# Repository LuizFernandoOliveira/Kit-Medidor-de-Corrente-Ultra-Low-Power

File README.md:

# Kit Medidor de Corrente Ultra-Low Power

## Descrição
Contendo quatro circuitos independentes de quatro topologias distintas, este circuito eletrônico é ideal para realizar a medição de corrente elétrica de diversas aplicação ultra-low power.

---

## Descrições técnicas

- Possui quatro circuitos independentes de corrente via transimpedância;
- Possui quatro circuitos independentes de corrente via rede T;
- Possui quatro circuitos independentes de corrente via High-Side;
- Possui quatro circuitos independentes de corrente via Low-Side;
- Possui alimentação de 3V3 ou 5V;
- Possui alimentação via USB tipo-C;
- Altíssima precisão e estabilidade: tensão de offset de 5 µV máx. a 25 °C, 8 µV em toda a faixa de temperatura (-40 °C a 125 °C);
- Entrada e saída rail-to-rail;
- Baixa tensão de alimentação: 1,8 - 5,5 V;
- Baixo consumo de energia: 40 µA máx. a 5 V;
- Produto ganho-largura de banda: 400 kHz;
- Alta tolerância a ESD: 4 kV HBM;
- Ampla faixa de temperatura de operação: -40 a 125 °C

---

## Estrutura do repositório
Os arquivos de hardware foram desenvolvidos utilizando o KiCad 9.0.
- **`.kicad_pcb`**: Layout da placa de circuito impresso (Board).
- **`.kicad_sch`**: Esquemático eletrônico do sistema (Schematic).
- **`.kicad_pro`**: Gerenciador de projeto do KiCad (Project).

---

## Autor
**Dr. Luiz Fernando Pinto de Oliveira**

*Engenheiro Eletrônico especializado em Sistemas Embarcados e Ultra-Low Power.*
- **Website:** [FAPLO](https://faplo.webnode.page/)
- **LinkedIn:** [lfpo](https://www.linkedin.com/in/lfpo/)

---

Shield: [![CC BY-NC-ND 4.0][cc-by-nc-nd-shield]][cc-by-nc-nd]

This work is licensed under a
[Creative Commons Attribution-NonCommercial-NoDerivs 4.0 International License][cc-by-nc-nd].

[![CC BY-NC-ND 4.0][cc-by-nc-nd-image]][cc-by-nc-nd]

[cc-by-nc-nd]: http://creativecommons.org/licenses/by-nc-nd/4.0/
[cc-by-nc-nd-image]: https://licensebuttons.net/l/by-nc-nd/4.0/88x31.png
[cc-by-nc-nd-shield]: https://img.shields.io/badge/License-CC%20BY--NC--ND%204.0-lightgrey.svg

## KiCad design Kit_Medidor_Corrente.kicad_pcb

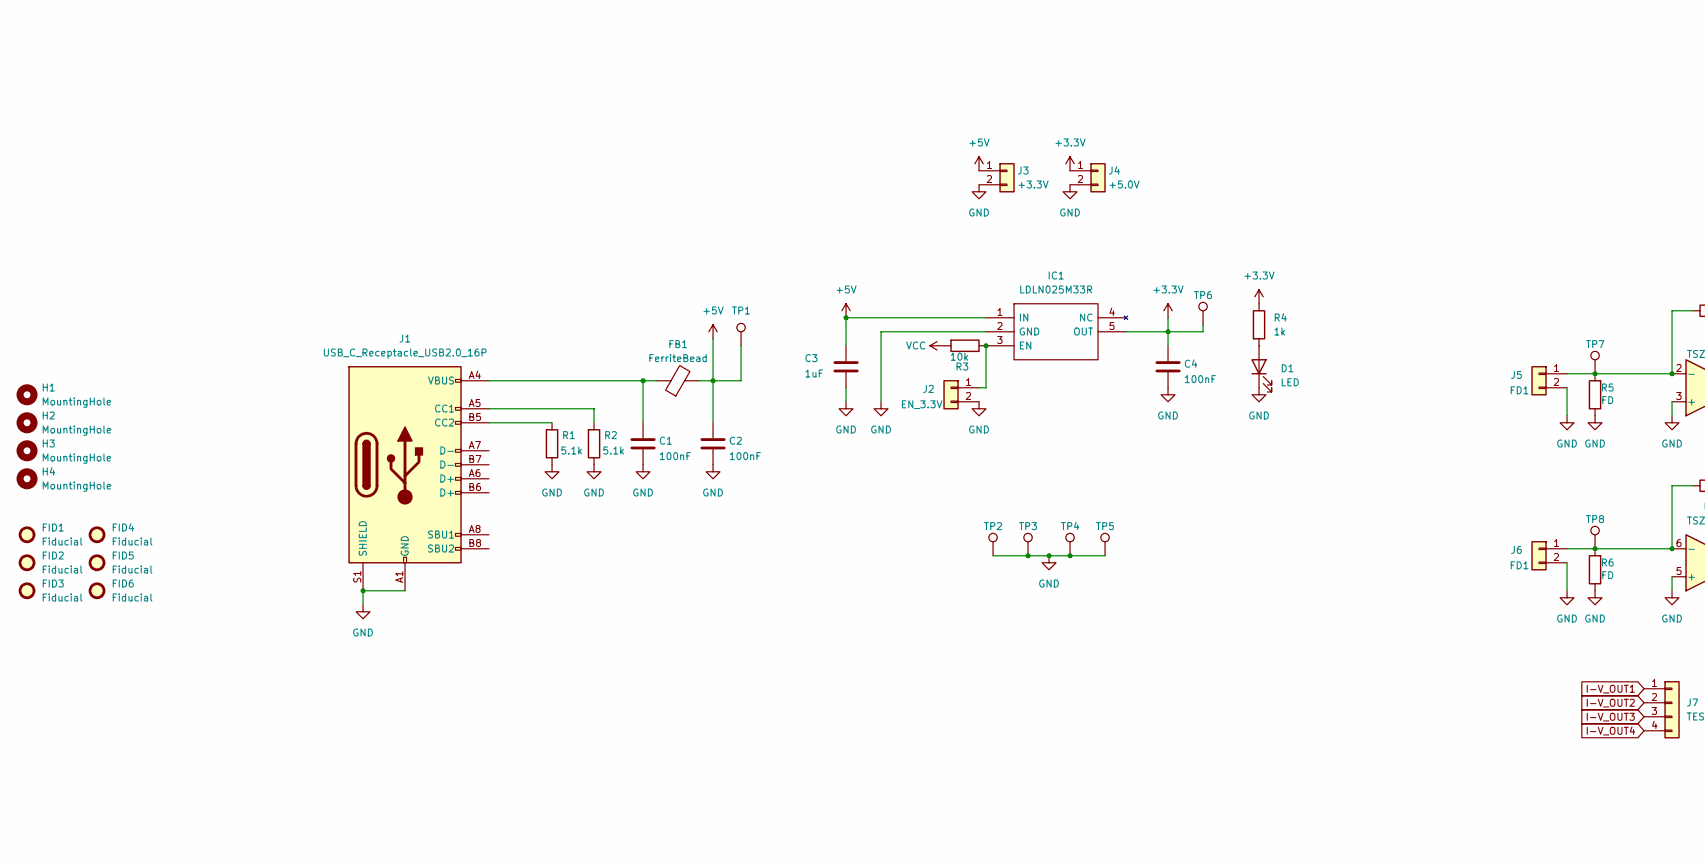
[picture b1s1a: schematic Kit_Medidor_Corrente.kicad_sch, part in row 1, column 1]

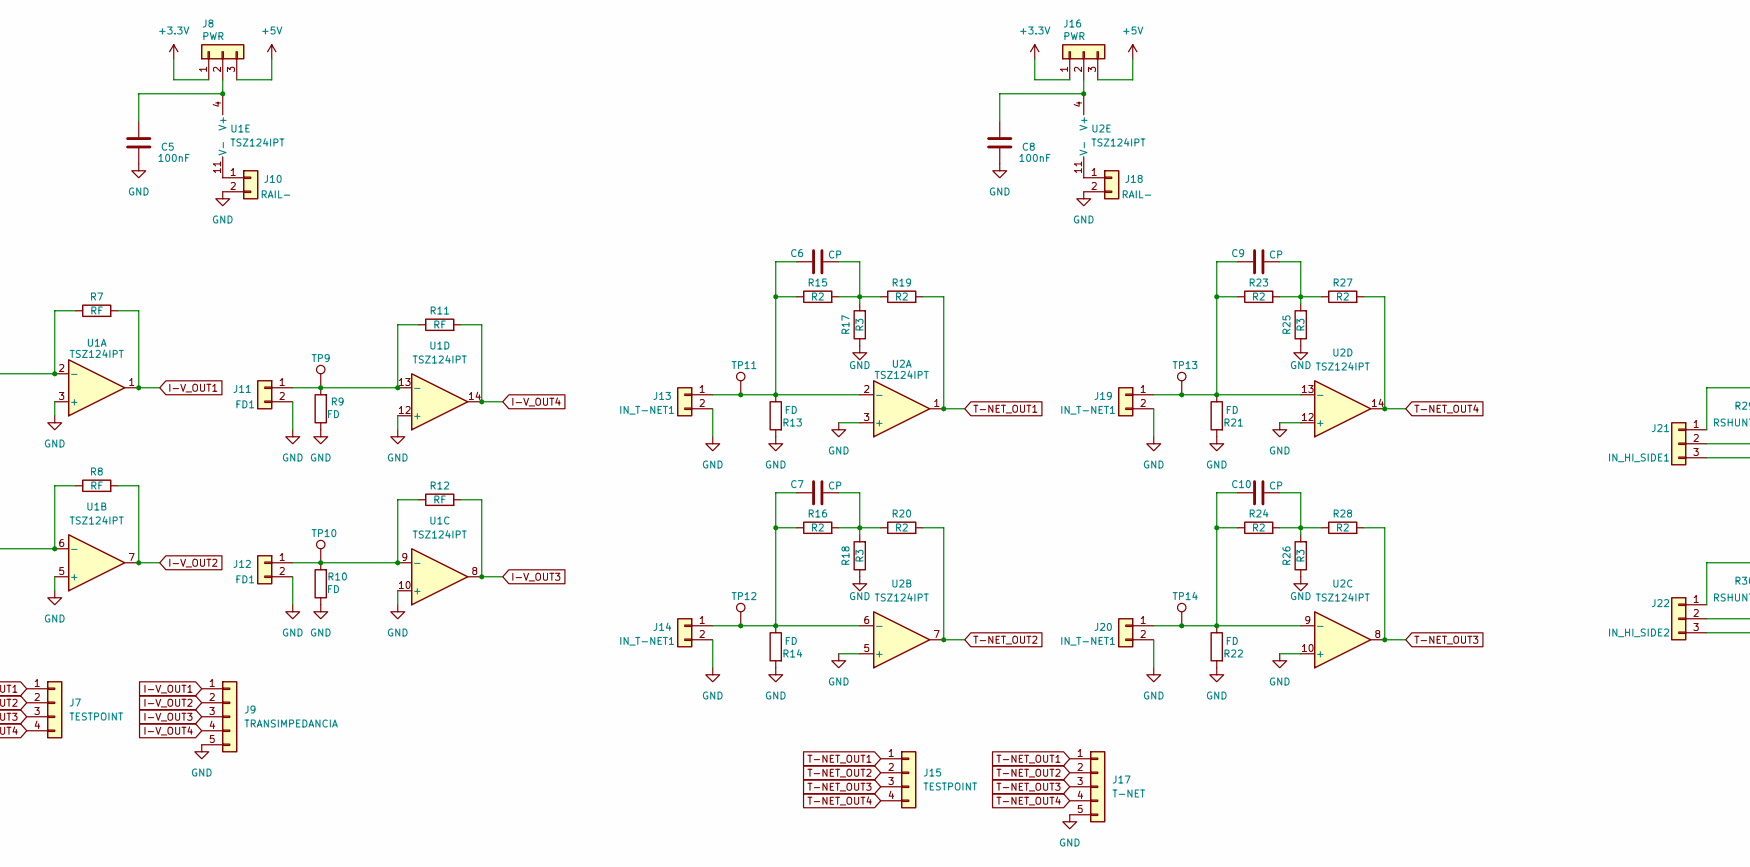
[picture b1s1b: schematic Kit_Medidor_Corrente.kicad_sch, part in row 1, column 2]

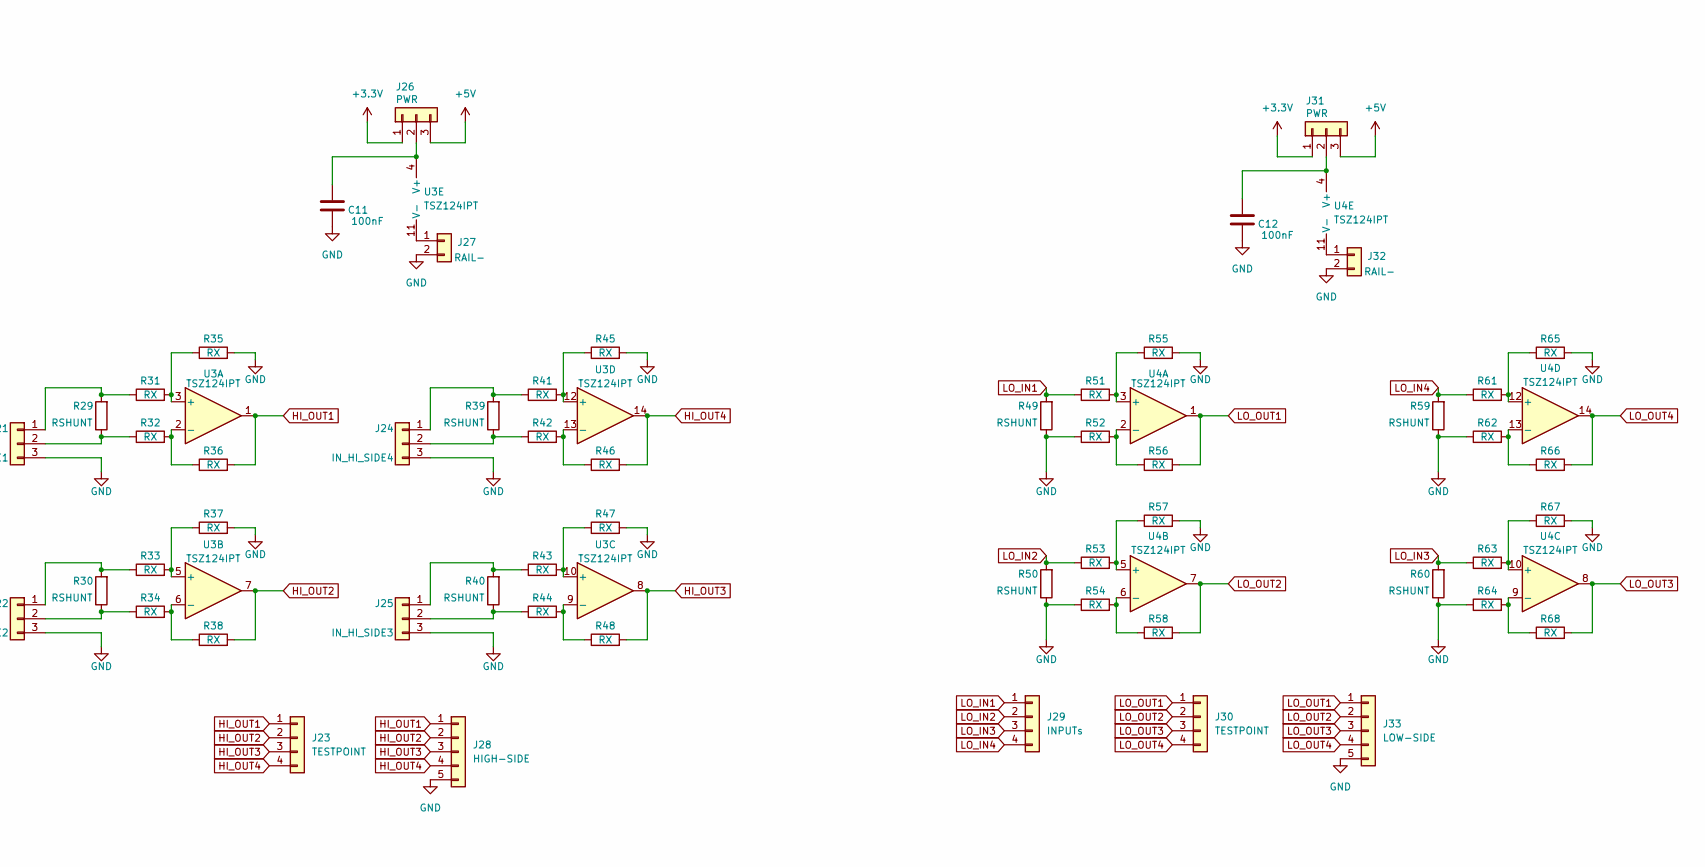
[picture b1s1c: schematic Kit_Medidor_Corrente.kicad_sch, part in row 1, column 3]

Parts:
C1, C2, C4, C5, C8, C11, C12: 100nF; C_0805_2012Metric
C3: 1uF; C_0805_2012Metric
C6, C7, C9, C10: CP; C_0805_2012Metric
D1: LED; LED_0805_2012Metric
FB1: FerriteBead; L_0805_2012Metric
FID1, FID2, FID3, FID4, FID5, FID6: Fiducial; Fiducial_1mm_Mask2mm
H1, H2, H3, H4: MountingHole; MountingHole_3.2mm_M3_DIN965
IC1: LDLN025M33R; SOT95P280X145-5N; Manufacturer_Part_Number LDLN025M33R; Mouser Part Number 511-LDLN025M33R
J1: USB_C_Receptacle_USB2.0_16P; USB_C_Receptacle_HRO_TYPE-C-31-M-12
J2: EN_3.3V; PinHeader_1x02_P2.54mm_Vertical
J3: +3.3V; PinHeader_1x02_P2.54mm_Vertical
J4: +5.0V; PinHeader_1x02_P2.54mm_Vertical
J5, J6, J11, J12: FD1; PinHeader_1x02_P2.54mm_Vertical
J7, J15, J23, J30: TESTPOINT; PinHeader_1x04_P2.54mm_Vertical
J8, J16, J26, J31: PWR; PinHeader_1x03_P2.54mm_Vertical
J9: TRANSIMPEDANCIA; PinHeader_1x05_P2.54mm_Vertical
J10, J18, J27, J32: RAIL-; PinHeader_1x02_P2.54mm_Vertical
J13, J14, J19, J20: IN_T-NET1; PinHeader_1x02_P2.54mm_Vertical
J17: T-NET; PinHeader_1x05_P2.54mm_Vertical
J21: IN_HI_SIDE1; PinHeader_1x03_P2.54mm_Vertical
J22: IN_HI_SIDE2; PinHeader_1x03_P2.54mm_Vertical
J24: IN_HI_SIDE4; PinHeader_1x03_P2.54mm_Vertical
J25: IN_HI_SIDE3; PinHeader_1x03_P2.54mm_Vertical
J28: HIGH-SIDE; PinHeader_1x05_P2.54mm_Vertical
J29: INPUTs; PinHeader_1x04_P2.54mm_Vertical
J33: LOW-SIDE; PinHeader_1x05_P2.54mm_Vertical
R1, R2: 5.1k; R_0805_2012Metric
R3: 10k; R_0805_2012Metric
R4: 1k; R_0805_2012Metric
R5, R6, R9, R10, R13, R14, R21, R22: FD; R_0805_2012Metric
R7, R8, R11, R12: RF; R_0805_2012Metric
R15, R16, R19, R20, R23, R24, R27, R28: R2; R_0805_2012Metric
R17, R18, R25, R26: R3; R_0805_2012Metric
R29, R30, R39, R40, R49, R50, R59, R60: RSHUNT; R_0805_2012Metric
R31, R32, R33, R34, R35, R36, R37, R38, R41, R42, R43, R44, R45, R46, R47, R48, R51, R52, R53, R54, R55, R56, R57, R58, R61, R62, R63, R64, R65, R66, R67, R68: RX; R_0805_2012Metric
TP1, TP2, TP3, TP4, TP5, TP6, TP7, TP8, TP9, TP10, TP11, TP12, TP13, TP14: TestPoint; TestPoint_Loop_D1.80mm_Drill1.0mm_Beaded
U1, U2, U3, U4: TSZ124IPT; SOP65P640X120-14N

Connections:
+3.3V: C4.1, IC1.5 (OUT), J4.1, J8.1, J16.1, J26.1, J31.1, R4.1, TP6.1
+5V: C2.1, C3.1, FB1.2, IC1.1 (IN), J3.1, J8.3, J16.3, J26.3, J31.3, TP1.1
GND: C1.2, C2.2, C3.2, C4.2, C5.1, C8.1, C11.1, C12.1, D1.1 (K), IC1.2 (GND), J1.A1 (GND), J1.A12 (GND), J1.B1 (GND), J1.B12 (GND), J1.S1 (SHIELD), J2.2, J3.2, J4.2, J5.2, J6.2, J9.5, J10.2, J11.2, J12.2, J13.2, J14.2, J17.5, J18.2, J19.2, J20.2, J21.3, J22.3, J24.3, J25.3, J27.2, J28.5, J32.2, J33.5, R1.1, R2.1, R5.1, R6.1, R9.1, R10.1, R13.2, R14.2, R17.1, R18.1, R21.2, R22.2, R25.1, R26.1, R35.2, R37.2, R45.2, R47.2, R49.1, R50.1, R52.1, R54.1, R55.2, R57.2, R59.1, R60.1, R62.1, R64.1, R65.2, R67.2, TP2.1, TP3.1, TP4.1, TP5.1, U1.3 (+), U1.5 (+), U1.10 (+), U1.12 (+), U2.3 (+), U2.5 (+), U2.10 (+), U2.12 (+)
HI_OUT1: J23.1, J28.1, R36.2, U3.1
HI_OUT2: J23.2, J28.2, R38.2, U3.7
HI_OUT3: J23.3, J28.3, R48.2, U3.8
HI_OUT4: J23.4, J28.4, R46.2, U3.14
I-V_OUT1: J7.1, J9.1, R7.2, U1.1
I-V_OUT2: J7.2, J9.2, R8.2, U1.7
I-V_OUT3: J7.3, J9.3, R12.2, U1.8
I-V_OUT4: J7.4, J9.4, R11.2, U1.14
LO_IN1: J29.1, R49.2, R51.1
LO_IN2: J29.2, R50.2, R53.1
LO_IN3: J29.3, R60.2, R63.1
LO_IN4: J29.4, R59.2, R61.1
LO_OUT1: J30.1, J33.1, R56.2, U4.1
LO_OUT2: J30.2, J33.2, R58.2, U4.7
LO_OUT3: J30.3, J33.3, R68.2, U4.8
LO_OUT4: J30.4, J33.4, R66.2, U4.14
unnamed: C1.1, FB1.1, J1.A4 (VBUS), J1.A9 (VBUS), J1.B4 (VBUS), J1.B9 (VBUS)
unnamed: C6.1, R15.2, R17.2, R19.1
unnamed: C7.1, R16.2, R18.2, R20.1
unnamed: C9.1, R23.2, R25.2, R27.1
unnamed: C10.1, R24.2, R26.2, R28.1
unnamed: D1.2 (A), R4.2
unnamed: IC1.3 (EN), J2.1, R3.1
unnamed: J1.A5 (CC1), R2.2
unnamed: J1.B5 (CC2), R1.2
unnamed: J5.1, R5.2, R7.1, TP7.1, U1.2 (-)
unnamed: J6.1, R6.2, R8.1, TP8.1, U1.6 (-)
unnamed: C5.2, J8.2, U1.4 (V+)
unnamed: J10.1, U1.11 (V-)
unnamed: J11.1, R9.2, R11.1, TP9.1, U1.13 (-)
unnamed: J12.1, R10.2, R12.1, TP10.1, U1.9 (-)
unnamed: C6.2, J13.1, R13.1, R15.1, TP11.1, U2.2 (-)
unnamed: C7.2, J14.1, R14.1, R16.1, TP12.1, U2.6 (-)
unnamed: C8.2, J16.2, U2.4 (V+)
unnamed: J18.1, U2.11 (V-)
unnamed: C9.2, J19.1, R21.1, R23.1, TP13.1, U2.13 (-)
unnamed: C10.2, J20.1, R22.1, R24.1, TP14.1, U2.9 (-)
unnamed: J21.1, R29.2, R31.1
unnamed: J21.2, R29.1, R32.1
unnamed: J22.1, R30.2, R33.1
unnamed: J22.2, R30.1, R34.1
unnamed: J24.1, R39.2, R41.1
unnamed: J24.2, R39.1, R42.1
unnamed: J25.1, R40.2, R43.1
unnamed: J25.2, R40.1, R44.1
unnamed: C11.2, J26.2, U3.4 (V+)
unnamed: J27.1, U3.11 (V-)
unnamed: C12.2, J31.2, U4.4 (V+)
unnamed: J32.1, U4.11 (V-)
unnamed: R31.2, R35.1, U3.3 (+)
unnamed: R32.2, R36.1, U3.2 (-)
unnamed: R33.2, R37.1, U3.5 (+)
unnamed: R34.2, R38.1, U3.6 (-)
unnamed: R43.2, R47.1, U3.10 (+)
unnamed: R44.2, R48.1, U3.9 (-)
unnamed: R41.2, R45.1, U3.12 (+)
unnamed: R42.2, R46.1, U3.13 (-)
unnamed: R51.2, R55.1, U4.3 (+)
unnamed: R52.2, R56.1, U4.2 (-)
unnamed: R53.2, R57.1, U4.5 (+)
unnamed: R54.2, R58.1, U4.6 (-)
unnamed: R63.2, R67.1, U4.10 (+)
unnamed: R64.2, R68.1, U4.9 (-)
unnamed: R61.2, R65.1, U4.12 (+)
unnamed: R62.2, R66.1, U4.13 (-)
T-NET_OUT1: J15.1, J17.1, R19.2, U2.1
T-NET_OUT2: J15.2, J17.2, R20.2, U2.7
T-NET_OUT3: J15.3, J17.3, R28.2, U2.8
T-NET_OUT4: J15.4, J17.4, R27.2, U2.14
VCC: R3.2

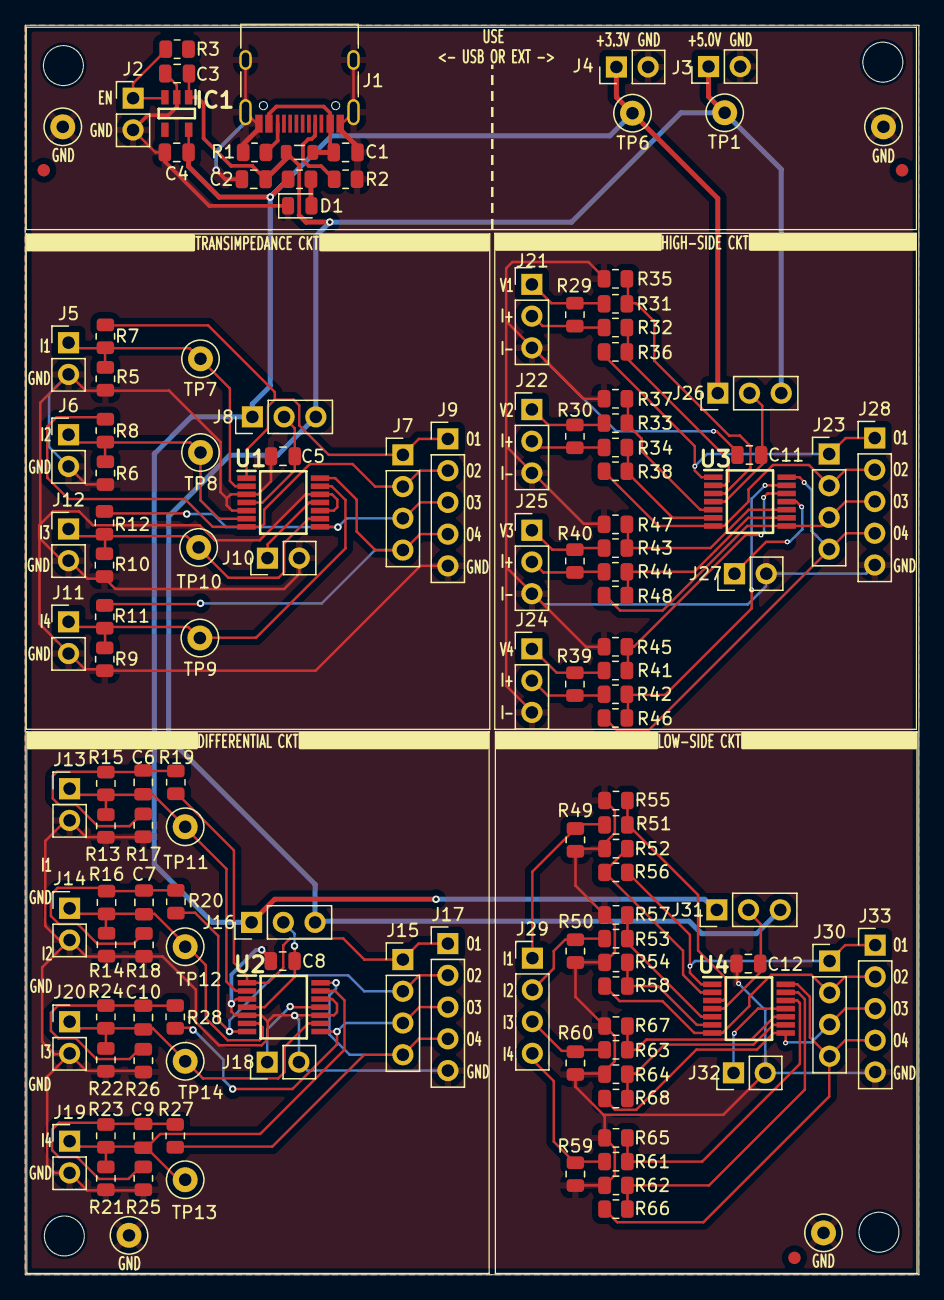
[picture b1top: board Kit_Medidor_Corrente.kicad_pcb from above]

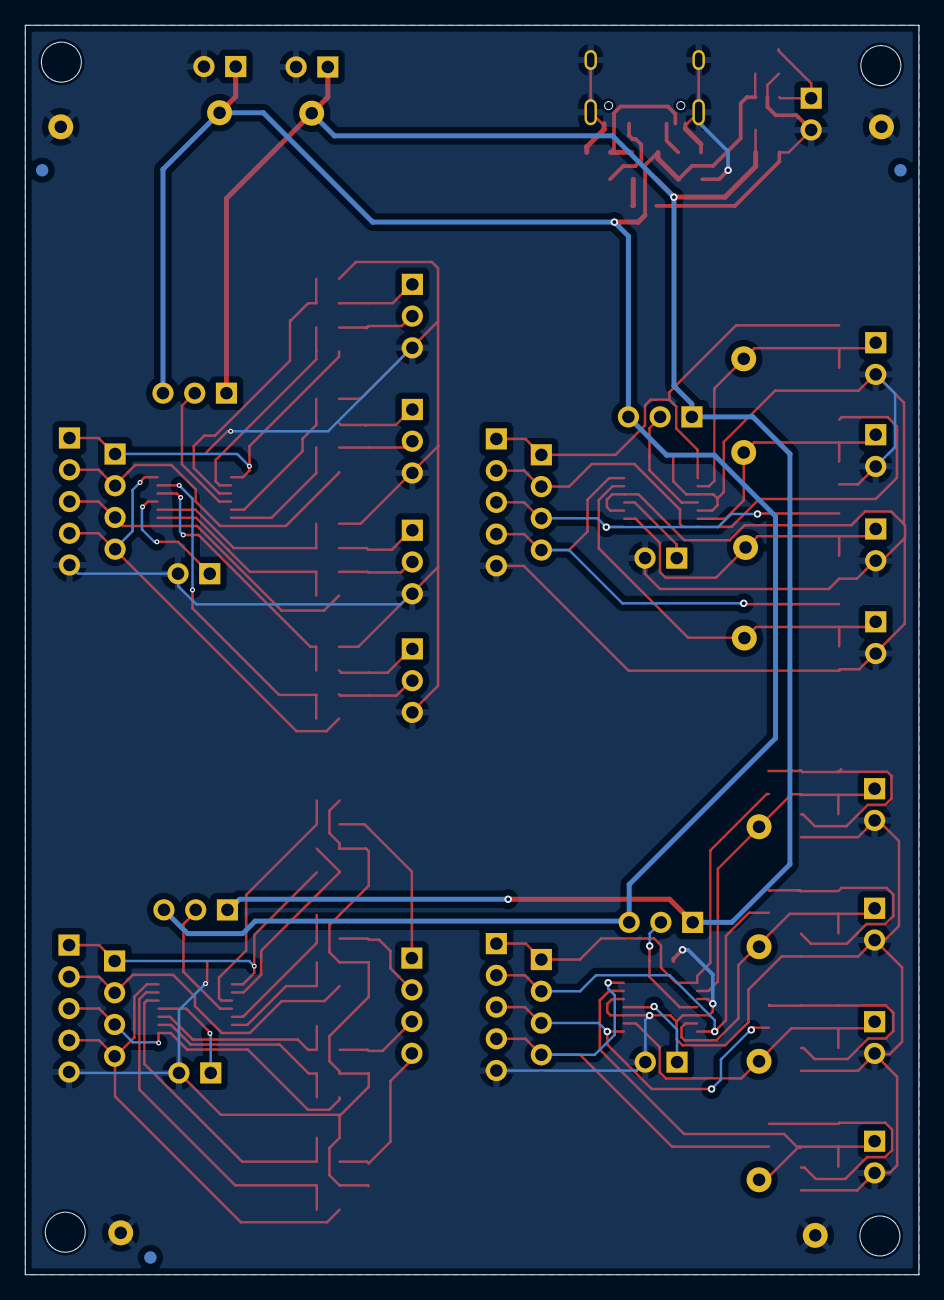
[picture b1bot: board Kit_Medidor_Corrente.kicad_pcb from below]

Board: 2 copper layers, 71.5 x 100.0 mm, 144 parts (3 on the bottom side), 72 nets.

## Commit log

2026-04-17 Inicialização de repositório
2026-04-17 Enhance README with project details and author info
    Added project status badges, technical descriptions, repository structure, and author information to the README.
2026-04-17 Add LICENSE file with CC BY-NC-ND 4.0
    Added the Creative Commons Attribution-NonCommercial-NoDerivatives 4.0 International Public License to the project.
